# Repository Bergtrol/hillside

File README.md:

# Hillside Ergonomic Keyboards

Hillside is a small family of split ergonomic keyboards.

The boards are the:

- [Hillside 56](hillside56) with a physical arrow T cluster fully separate from the alpha keys. The most novice friendly, but the largest.
- [Hillside 52](hillside52) with ring and pinky splay and whose physical arrow keys steal one of the alpha keys. The best all around choice.
- [Hillside 48](hillside48) which is like a Ferris Sweep on steroids. The original and most compact.

Their key differences are:

| Board      | Layout  | Arrow <br> T | Finger <br> Splay | Encoder <br> Spots / Side | Hotswap <br> Option| Thin <br> Layout | Thin <br> Size |
|:------------|:--------|:--------:|:---------:|:---------:|:-------:|:-------:|:-------:|
| [Hillside 56](hillside56) | 3x6+5+5 | yes      |  no       | 4         | yes     | 3x5+4+5 | 48 |
| [Hillside 52](hillside52) | 3x6+3+5 | yes      |  yes      | 3         | yes     | 3x5+2+5 | 44 |
| [Hillside 48](hillside48) | 3x6+1+5 | no       |  no       | 1         | no      | 3x5+1+5 | 42 |

Their common features are:

- Choc-spaced keys, aggressive stagger, five thumb keys
- Break-off pinky column
- Tenting puck support
- QMK and ZMK firmware
- Nice!nano battery power switch
- Encoder support for one per side
- Haptic feedback header and mount
- Underglow from five SK6812-MINI-Es
- Reversible PCB which qualifies for AllPCB's free PCB
- Detailed BOM and default keyboard rational
- SMT diodes, resistors, capacitors, and reset switch

See the board readmes for details and default keymaps.

*Keycaps*: Hillside boards are _only_ suitable for choc v1 switches and keycaps based on an 18 x 17mm switch spacing, such as the [MBK](https://mkultra.click/mbk-choc-keycaps), [Lowprokb LDSA](https://lowprokb.ca/products/ldsa-low-profile-blank-keycaps) and [MoErgo MCC](https://mkultra.click/moergo-mcc-pom-1u-keycap/) keycaps. Not MX ones, nor 18 x 18mm ones such as Work Louder, nor Kailh Choc Transparent keycaps.

## Hardware

See the [wiki](https://github.com/mmccoyd/hillside/wiki)
  for how to order PCBs and build the boards.

See [Forking and Modifying](https://github.com/mmccoyd/hillside/wiki/Forking%20and%20Modifying)
  on whether it would be difficult to modify these designs.

## Firmware

QMK includes firmware for [Hillside48](https://github.com/qmk/qmk_firmware/tree/master/keyboards/handwired/hillside).

ZMK firmware is at [Hillside ZMK Firmware](https://github.com/mmccoyd/zmk-config).

The default keymap is shared by both and is described in QMK.

## Acknowledgments

The awesome discord communities for Low Profile Keyboards and splitkb.com provided a fertile learning ground.
Several of the symbol and footprint files came from that community, as noted in the doc folder.
The keyboards I have used and read about also influenced these boards, including the
  [Atreus](https://shop.keyboard.io/products/keyboardio-atreus),
  [Lily58](https://github.com/kata0510/Lily58),
  [Kyria](https://splitkb.com/collections/keyboard-kits/products/kyria-pcb-kit),
  [Corne](https://github.com/foostan/crkbd) and
  [Ferris](https://github.com/pierrechevalier83/ferris).

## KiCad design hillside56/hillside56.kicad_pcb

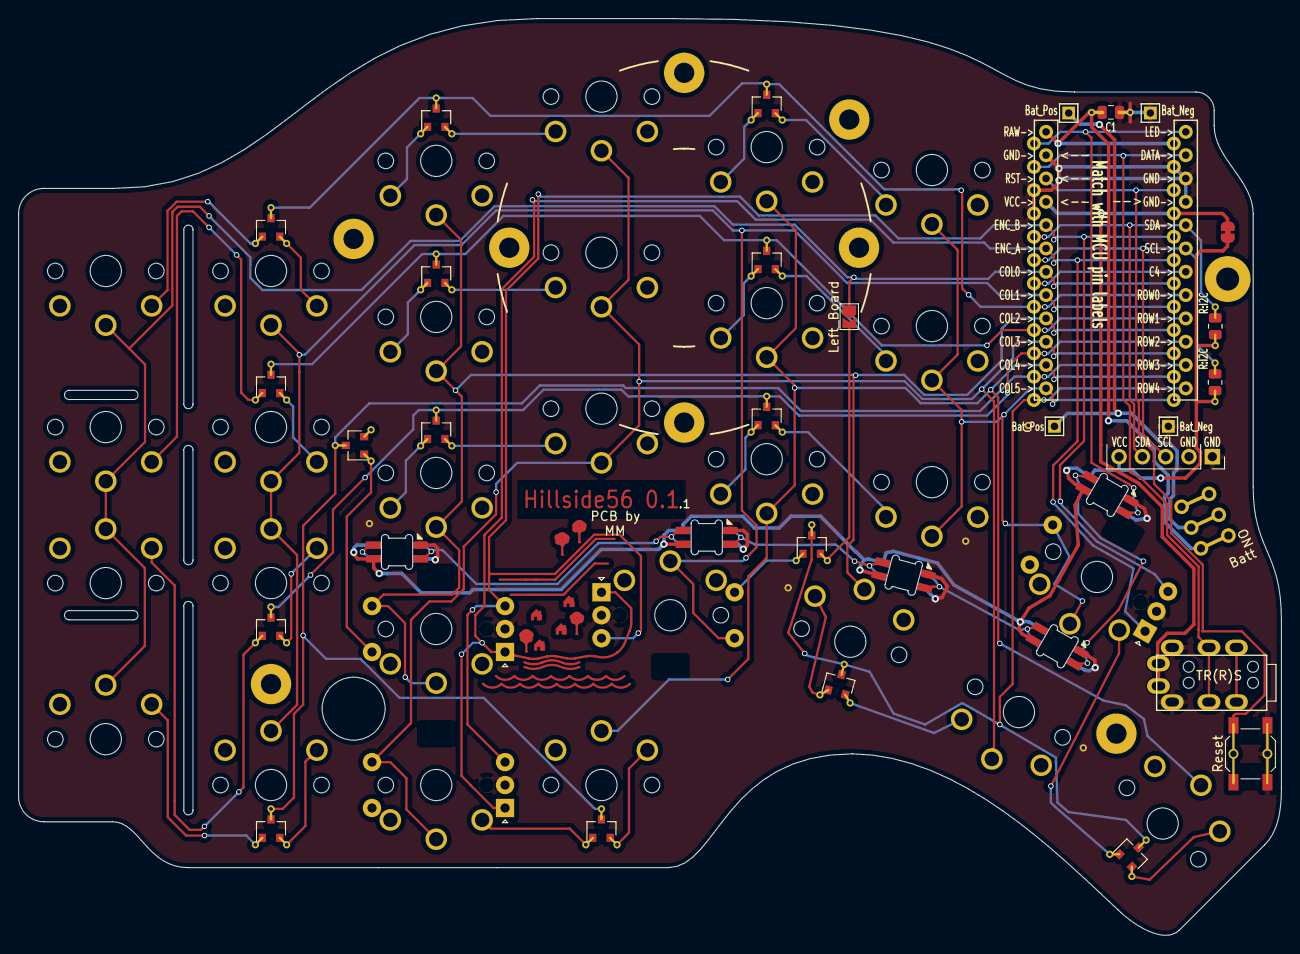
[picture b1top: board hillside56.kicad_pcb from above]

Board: 2 copper layers, 137.6 x 99.9 mm, 89 parts (0 on the bottom side), 56 nets.

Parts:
C1: 4u7; C_0805_2012Metric
D1, D2, D3, D4, D5: SK6812-MINI-E
D7, D8, D9, D10, D11, D12, D13, D14, D15, D16, D17, D18, D19, D20, D21: BAV70; SOT-23
H1: Mount_Tenting; Tenting_Puck
H2, H8, H9, H10, H11, H12, H13, H14, H15, H16, H17, H18, H19, H20, H21, H22: Bumpon
H3: Logo; Hillside_Logo
H4, H5, H6, H7: MountHole; MountingHole_2.2mm_with_PCB_insert_rings
J1: Haptic; Pimoroni_Haptic
J2: TRRS; MJ-4PP-9
J3, J5: Bat_Pos; 1pin_conn
J4, J6: Bat_Neg; 1pin_conn
JP1: VccJumper; SolderJumper-2_P1.3mm_Bridged_RoundedPad1.0x1.5mm
JP2: Left_Board; SolderJumper-2_P1.3mm_Open_TrianglePad1.0x1.5mm
K1, K2, K3, K4, K5, K6, K7, K8, K9, K10, K11, K12, K13, K14, K15, K16, K17, K18, K20, K21, K24, K26, K27, K28: SW_Key; pg1350-R_hotswap
K19, K22, K23, K25: SW_Rotary; pg1350-DR_rotary_hotswap
R1, R2: R:I2C; R_0805_2012Metric
SW1: Reset; SW_SPST_SKQG_WithStem
SW2: SW_Power; SW_SPDT_JS202011AQN
U1: ProMicro_r; ProMicro_v2
V1, V2, V3, V4, V5: Via; VIA-0.8mm

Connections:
GND: C1.2, D1.3 (VSS), D2.3 (VSS), D3.3 (VSS), D4.3 (VSS), D5.3 (VSS), J1.1, J1.2, J2.T (Tip), J4.1, J6.1, K19.C, K22.C, K23.C, K25.C, SW1.2, U1.3 (GND), U1.4 (GND), U1.23 (GND), V1.1 (via), V2.1 (via), V3.1 (via), V4.1 (via), V5.1 (via)
LED: D1.4 (DIN), U1.1 (D3/TX0)
unnamed: D1.2 (DOUT), D2.4 (DIN)
unnamed: D2.2 (DOUT), D3.4 (DIN)
unnamed: D3.2 (DOUT), D4.4 (DIN)
unnamed: D4.2 (DOUT), D5.4 (DIN)
unnamed: D7.1 (A1), K1.2
unnamed: D7.2 (A2), K2.2
unnamed: D8.1 (A1), K3.2
unnamed: D8.2 (A2), K4.2
unnamed: D9.1 (A1), K5.2
unnamed: D9.2 (A2), K6.2
unnamed: D10.1 (A1), K7.2
unnamed: D10.2 (A2), K8.2
unnamed: D11.1 (A1), K9.2
unnamed: D11.2 (A2), K10.2
unnamed: D12.1 (A1), K11.2
unnamed: D12.2 (A2), K12.2
unnamed: D13.1 (A1), K13.2
unnamed: D13.2 (A2), K14.2
unnamed: D14.1 (A1), K15.2
unnamed: D14.2 (A2), K16.2
unnamed: D15.1 (A1), K17.2
unnamed: D15.2 (A2), K18.2
unnamed: D16.1 (A1), K20.2
unnamed: D16.2 (A2), K21.2
unnamed: D17.1 (A1), K22.S2
unnamed: D18.1 (A1), K23.S2
unnamed: D18.2 (A2), K24.2
unnamed: D19.1 (A1), K25.S2
unnamed: D19.2 (A2), JP2.2 (B)
unnamed: D20.1 (A1), K26.2
unnamed: D20.2 (A2), K27.2
unnamed: D21.1 (A1), K19.S2
unnamed: D21.2 (A2), K28.2
SCL: J1.3, R1.2, U1.6 (SCL/D0/3)
SDA: J1.4, R2.2, U1.5 (SDA/D1/2)
VCC: J2.S (Sleeve), JP1.1 (A), U1.21 (VCC)
VCC_ACC: D1.1 (VDD), D2.1 (VDD), D3.1 (VDD), D4.1 (VDD), D5.1 (VDD), J1.5, JP1.2 (B), R1.1, R2.1
bat+: J3.1, J5.1, SW2.2 (B)
col0: JP2.1 (A), K1.1, K7.1, K13.1, K20.1, U1.18 (A1/F6)
col1: K2.1, K8.1, K14.1, K21.1, K25.S1, U1.17 (A0/F7)
col2: K3.1, K9.1, K15.1, K22.S1, K26.1, U1.16 (15/B1)
col3: K4.1, K10.1, K16.1, K23.S1, K27.1, U1.15 (14/B3)
col4: K5.1, K11.1, K17.1, K24.1, K28.1, U1.14 (16/B2)
col5: K6.1, K12.1, K18.1, K19.S1, U1.13 (10/B6)
data: J2.R1 (Ring1), U1.2 (D2/RX1)
enc_a: K19.A, K22.A, K23.A, K25.A, U1.19 (A2/F5)
enc_b: K19.B, K22.B, K23.B, K25.B, U1.20 (A3/F4)
raw: C1.1, SW2.3 (C), U1.24 (RAW)
reset: SW1.1, U1.22 (RST)
row0: D7.3 (K), D8.3 (K), D9.3 (K), U1.8 (C6/5)
row1: D10.3 (K), D11.3 (K), D12.3 (K), U1.9 (D7/6)
row2: D13.3 (K), D14.3 (K), D15.3 (K), U1.10 (E6/7)
row3: D16.3 (K), D17.3 (K), D18.3 (K), U1.11 (B4/8)
row4: D19.3 (K), D20.3 (K), D21.3 (K), U1.12 (B5/9)

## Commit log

2022-01-14 Hill52 Initial: copy from Hillside
2022-01-14 Hill52 Initial: rename files and internal links
2022-01-14 Move alpha-key row nets up one pin on MCU
2022-01-14 Add two lower pinkie keys, update outer edge cut
2022-01-15 schema: Encoder wired into extra row, not thumb's
2022-01-18 Handedness Jumper. Rotate lower pinkies for bumpon
    - Bat_Neg pads not Bat_GND
2022-01-24 Footprint: Bumpon
2022-01-24 Symbol: Bumpon
2022-01-24 Footprint: Mounting hole with PCB insert rings
2022-01-24 Footprint: Promicro one more row pin label
2022-01-24 Footprint: Holes of promicro for bottom plate
2022-01-24 Footprint: Holes of key switch for bottom plate
2022-01-24 Hillside56 Arrow clusters. Four encoder spots/side
    - Two additional keys per side to form arrow cluster
    - Mark where bumpons fit on board bottom around edge and components
    - Mounting holes set for use with PCB threaded inserts in bottom plate
    - Handedness jumper in key matrix
    - Extend edgecut 0.75 mm for more space for a bottom plate with cutouts
    - Rotate several keys for more bumpon room around edge
2022-01-24 Project file: Layer view presets Gerber and Clean
2022-01-24 Rename to Hillside56, update files
2022-01-24 Rename model directory
2022-01-24 - ignore file KiCad 6 notes
2022-01-24 ref: PCB threaded insert specs
2022-01-24 - minor arc diffs from reopening
2022-01-24 - ignore gerber, .svg, .dxf files in output dir
2022-01-24 Hillside56 v0.1.0-alpha
    - 'Cut Out' for interior edge cut
    - Update sheet dates to today
2022-01-24 Gerbers Hillside56 v0.1.0-alpha
2022-01-24 Remove gerbers
2022-01-24 - tweak switch symbol locations in arrow cluster
2022-01-24 - Readme within gerber folder
2022-01-24 - update sheet descriptions
2022-02-07 Move hillside original board into hillside48/
2022-02-07 Reorg: docs into 48, 48 and lib to top level
2022-02-07 Split readme into family and board
2022-02-08 - Tweak readme
2022-02-08 - re-org fixup: re-add kicad and kicad/lib
2022-02-08 - re-org fixup: move hillside56 to top level
2022-02-08 - re-org fixup: move lib/ to top level
2022-02-08 -re-org: move license refs to top level doc/
2022-02-20 Remove alpha designation
2022-02-21 Docs: Hilside56 writup, images, main keymap
2022-03-26 - readme: grammer
2022-03-26 52 Hill52 Initial: copy from 56
2022-03-26 52 Initial: change 56 to 52
2022-03-26 52: Remove extra keys, Splay 5 and 10, pinky align
2022-03-27 Footprint: Switch with hotswap sized pads
2022-03-27 Footprint: Switch rotary, trim courtyard area
2022-03-27 Footprint: Logo trim wave extent
2022-03-27 Footprint: Switch rotary: hotswap pads
2022-03-27 52: Doc: Gerber readme update, drill sizes, ignore
2022-03-28 56: KiCad 6.0.4 open, fill, DRC and save
2022-03-28 56: Breakaway tracks on edges, extra break slots
2022-03-28 56 PCB: Use hotswap switches, bump version number
2022-03-28 56: Scheme use hotswap switches
2022-03-28 56: Reference 50 mm ruler
2022-03-28 - 56: Reference ruler force to show millimeters
2022-03-28 52: Hotswap footprints, cleanup tracks
    - Move base mount, and diode, closer to edge
    - PCB: tweak scale ruler, cleanup traces across splays, broken tracks
    - Scheme: Trim switch numbers, Hotswap footprints
    - Use switches with larger pads for hotswap
    - KiCad 6.0.4 and save/load churn
2022-04-05 Readme shows differences in table
2022-04-10 52 doc: changelog
2022-04-10 48 doc: keyboard-layout-editor template
2022-04-24 Fam readme: add 52 and family photo
2022-04-24 52: readme photo
2022-04-25 52 tweak readme. remove image
2022-04-25 52 readme link smaller keymap image
2022-04-25 52 readme tweak
2022-04-25 52 readme fix links, lists, tweak
2022-04-25 Fam readme fix links, tweak keycaps
2022-04-25 fam readme tweak
2022-04-25 readme keycap tweak
2022-04-25 Readme keymap smaller image
2022-05-09 52: Readme link to images
2022-05-09 52: Images of PCB, schematic, switches, render
2022-05-09 Fam: Remove images now in wiki
2022-05-09 52: Readme tweak for nighttime background
2022-05-25 Added CircuitPython KMK firmware implementation for hand-wired version running RPPico
